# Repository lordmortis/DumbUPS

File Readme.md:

DumbUPS - A really stupid UPS daemon for really stupid UPSs
=====================

This is a go project and firmware for interfacing with UPSs that don't have modern interfaces. 
Why? they are perfectly fine and often available second hand :)

However, this is only tested against a APC BackUPS Pro 1400 via the example arduino-based interface device,
but the existing interface should work for most dumb UPS's.

Go Program
=======
The go part of this project (this directory) has two commands:
 
 * `monitor` 
   a continuously running process that reads the  
   serial port that's connected to the UPS interface microcontroller (see Protocol below). 
   It will also emit a "pong" command every 10 seconds to reset the watchdog timer
 * `shutdown`
   send the "shut" command to the micro to turn off the power.

The [config](dumbups.conf.sample) file requires the serial port. 
The monitor daemon will use the optional "shutdown" config option to specify if it will issue a shutdown upon power loss (the default) or low battery

The Protocol
====

The protocol is very simple, the UPS interface outputs lines of text representing the state:
```
STATUS-BATT:<bool>,BATTLOW:<bool>,MAINSDWN:<bool>,MAINSUP:<bool>\n
```

where <bool> is either "Yes" or "No" if that line is high.

There is a 30-second watchdog timer, where if no command is received for this period and the UPS has no power, it will turn off.

Commands:
 * `shut` - start the power off sequence if the mains power is off
 * `noshut` - cancel a power off sequence
 * `ping` - a no-op that resets the watchdog timer

UPS Interfaces
====

 * [APC - Arduino](Arduino/APC_Interface/Readme.md)
   * This implementation example uses an arduino (specifically a [LeoStick](https://www.freetronics.com.au/products/leostick)) but should be simple enough to serve as an example for other interfaces
 * [APC - attiny2312](attiny2313/Readme.md)
   * This implementation is for an [attiny2313](https://ww1.microchip.com/downloads/en/DeviceDoc/Atmel-2543-AVR-ATtiny2313_Datasheet.pdf) - which is a much simpler micro. Also includes Schematics and Gerbers for a PCB!

Linux Service
====
There is an example systemd file for running this as a linux service [here](systemd/dumbups.service)

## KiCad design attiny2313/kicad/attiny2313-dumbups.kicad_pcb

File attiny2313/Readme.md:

DumbUPS - Firmware for APC Dumb ups interface (attiny version)
=====================

This repo contains a platformio project to provide a DumbUPS serial interface for a APC UPS that uses the dumb interface.

This uses [Attiny2313V-10PU](https://ww1.microchip.com/downloads/en/DeviceDoc/Atmel-2543-AVR-ATtiny2313_Datasheet.pdf) and a [FTDI MM232R USB dev board](https://ftdichip.com/products/mm232r/) instead of a Leostick. 
I think this is a much smaller physical layout, with cheaper components and no surface mount, so this is easy to make.

Included is the [Kicad Project](kicad)

 * [Schematic](Schematic.pdf)
 * [PCB Layout](PCB.pdf)
 
Pinouts
=

| Signal        | AVR Pin       | Direction  | APC DB-9 Pin       | 
|---------------|---------------|------------|--------------------|
| Battery Power | 12 (Port B 0) | To AVR     | 2                  |
| Mains Down    | 13 (Port B 1) | To Arduino | 3 (Open Collector) |
| Ground        | 10 (Gnd)      | n/a        | 4                  |
| Low Battery   | 14 (Port B 2) | To Arduino | 5 (Open Collector) |
| Mains Up      | 15 (Port B 3) | To Arduino | 6 (Open Collector) |
| Power State   | 5 (Port A 0)  | To APC     | 7                  |

(thanks to [APCUPSD](http://apcupsd.org/manual/manual.html#voltage-signalling) for this info, made life a lot easier!)

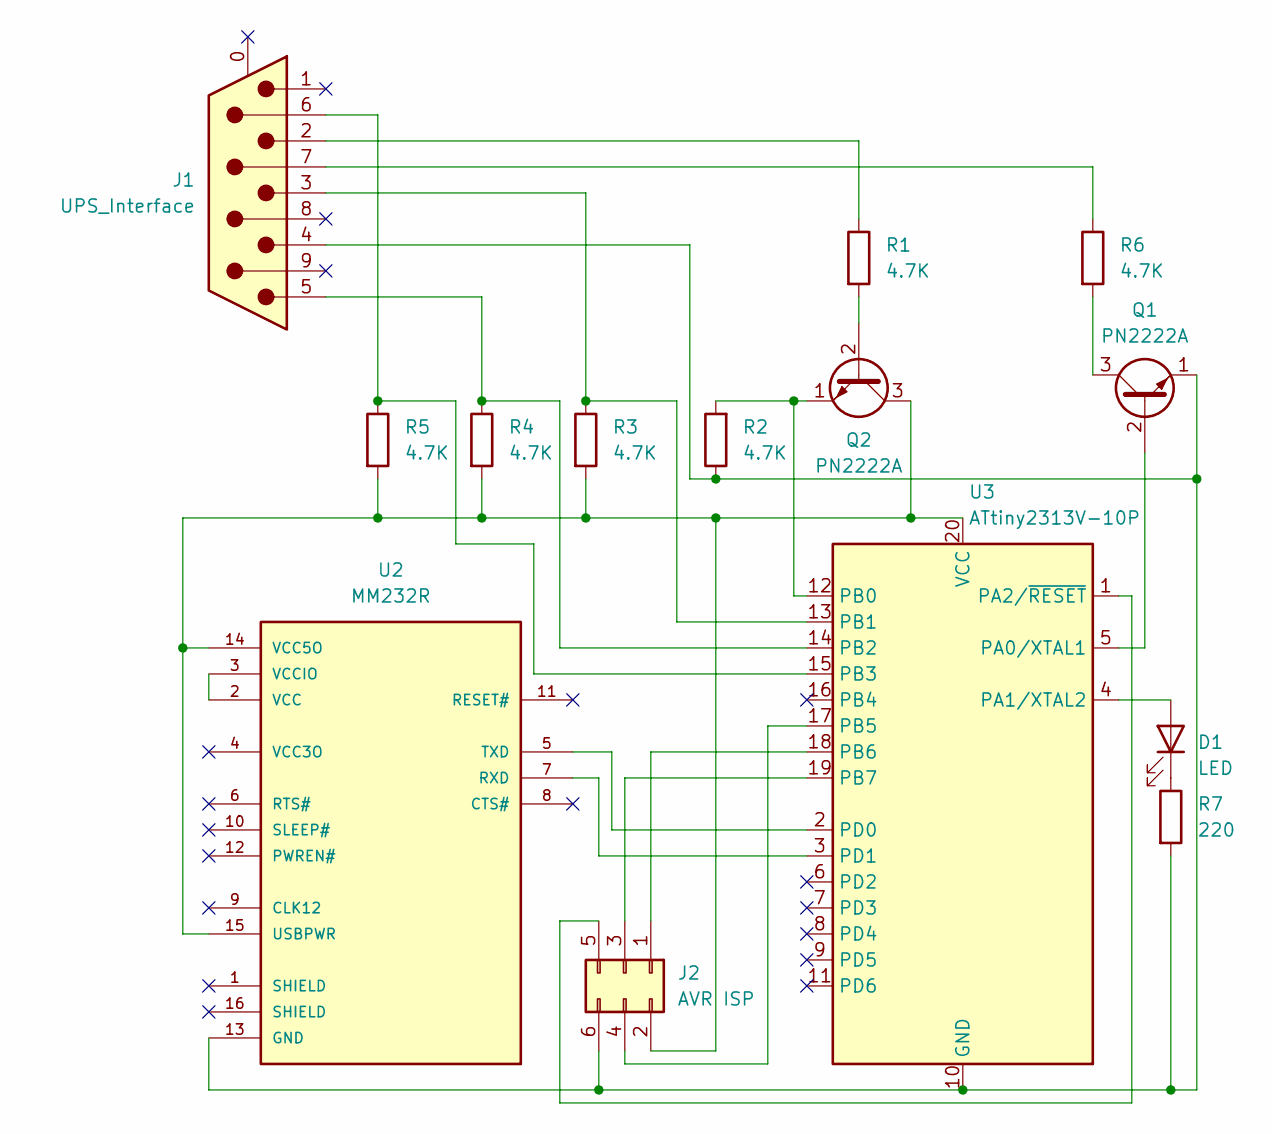
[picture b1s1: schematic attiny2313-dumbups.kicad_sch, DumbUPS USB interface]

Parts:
D1: LED; PinHeader_1x02_P2.54mm_Vertical
J1: UPS_Interface; DSUB-9_Male_Horizontal_P2.77x2.84mm_EdgePinOffset7.70mm_Hou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
J2: AVR ISP; IDC-Header_2x03_P2.54mm_Vertical
Q1: PN2222A; TO-92L_Inline
Q2: PN2222A; TO-92_Inline
R1, R2, R3, R4, R5, R6: 4.7K; R_Axial_DIN0207_L6.3mm_D2.5mm_P10.16mm_Horizontal
R7: 220; R_Axial_DIN0207_L6.3mm_D2.5mm_P10.16mm_Horizontal
U2: MM232R; FTDI_MM232R; PARTREV 1.2
U3: ATtiny2313V-10P; DIP-20_W7.62mm

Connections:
unnamed: D1.1 (K), R7.1
unnamed: D1.2 (A), U3.4 (PA1/XTAL2)
unnamed: J1.2, R1.1
unnamed: J1.3, R3.1, U3.13 (PB1)
unnamed: J1.4, J2.6, Q1.1 (E), R2.1, R7.2, U2.13 (GND), U3.10 (GND)
unnamed: J1.5, R4.1, U3.14 (PB2)
unnamed: J1.6, R5.1, U3.15 (PB3)
unnamed: J1.7, R6.1
unnamed: J2.1, U3.18 (PB6)
unnamed: J2.2, Q2.3 (C), R3.2, R4.2, R5.2, U2.14 (VCC5O), U2.15 (USBPWR), U3.20 (VCC)
unnamed: J2.3, U3.19 (PB7)
unnamed: J2.4, U3.17 (PB5)
unnamed: J2.5, U3.1 (PA2/~RESET)
unnamed: Q1.2 (B), U3.5 (PA0/XTAL1)
unnamed: Q1.3 (C), R6.2
unnamed: Q2.1 (E), R2.2, U3.12 (PB0)
unnamed: Q2.2 (B), R1.2
unnamed: U2.2 (VCC), U2.3 (VCCIO)
unnamed: U2.5 (TXD), U3.2 (PD0)
unnamed: U2.7 (RXD), U3.3 (PD1)

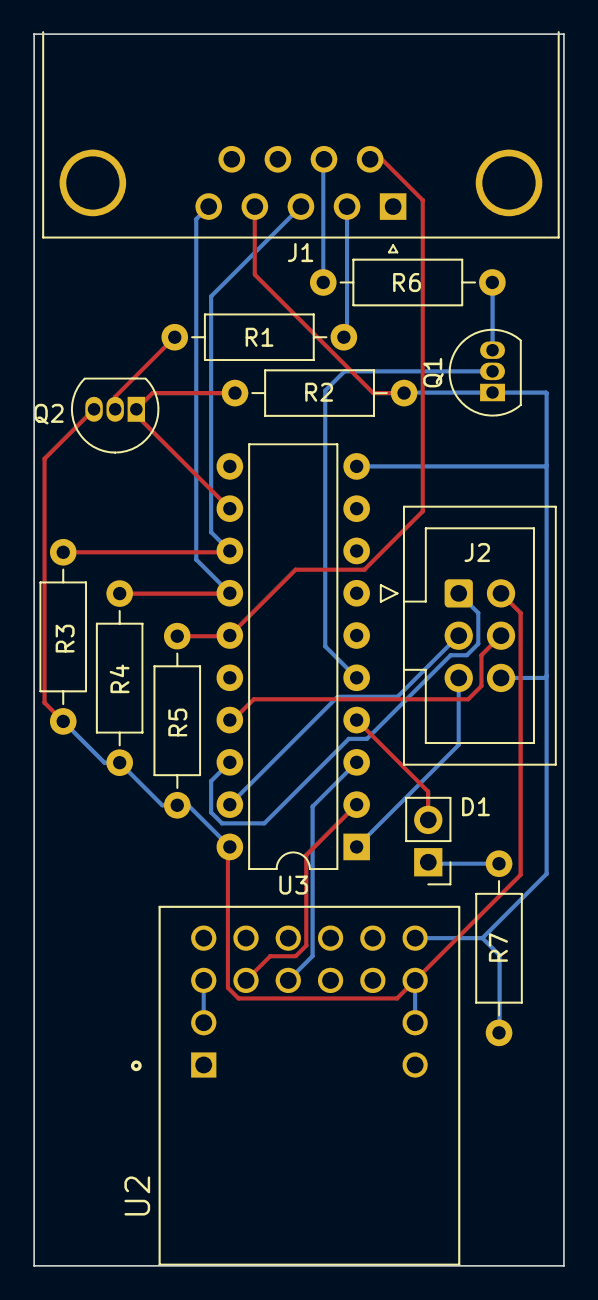
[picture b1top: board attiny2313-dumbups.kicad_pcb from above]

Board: 2 copper layers, 31.8 x 74.0 mm, 14 parts (0 on the bottom side), 20 nets.

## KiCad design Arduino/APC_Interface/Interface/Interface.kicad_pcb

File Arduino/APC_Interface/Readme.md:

DumbUPS - Firmware for APC Dumb ups interface
=====================

This repo contains a platformio project to provide a DumbUPS serial interface for a APC UPS that uses the dumb interfaces

The circuit for this is [here](Schematic.pdf)

Pinouts
=

| Signal        | Arduino Pin | Direction  | APC DB-9 Pin        |
|---------------|-------------|------------|---------------------|
| Battery Power | 8           | To Arduino | 2                   |
| Mains Down    | 10          | To Arduino | 3 (Open Collector)  |
| Ground        | Gnd         | n/a        | 4                   |
| Low Battery   | 9           | To Arduino | 5 (Open Collector)  |
| Mains Up      | 11          | To Arduino | 6  (Open Collector) |
| Power State   | 12          | To APC     | 7                   |

(thanks to [APCUPSD](http://apcupsd.org/manual/manual.html#voltage-signalling) for this info, made life a lot easier!)

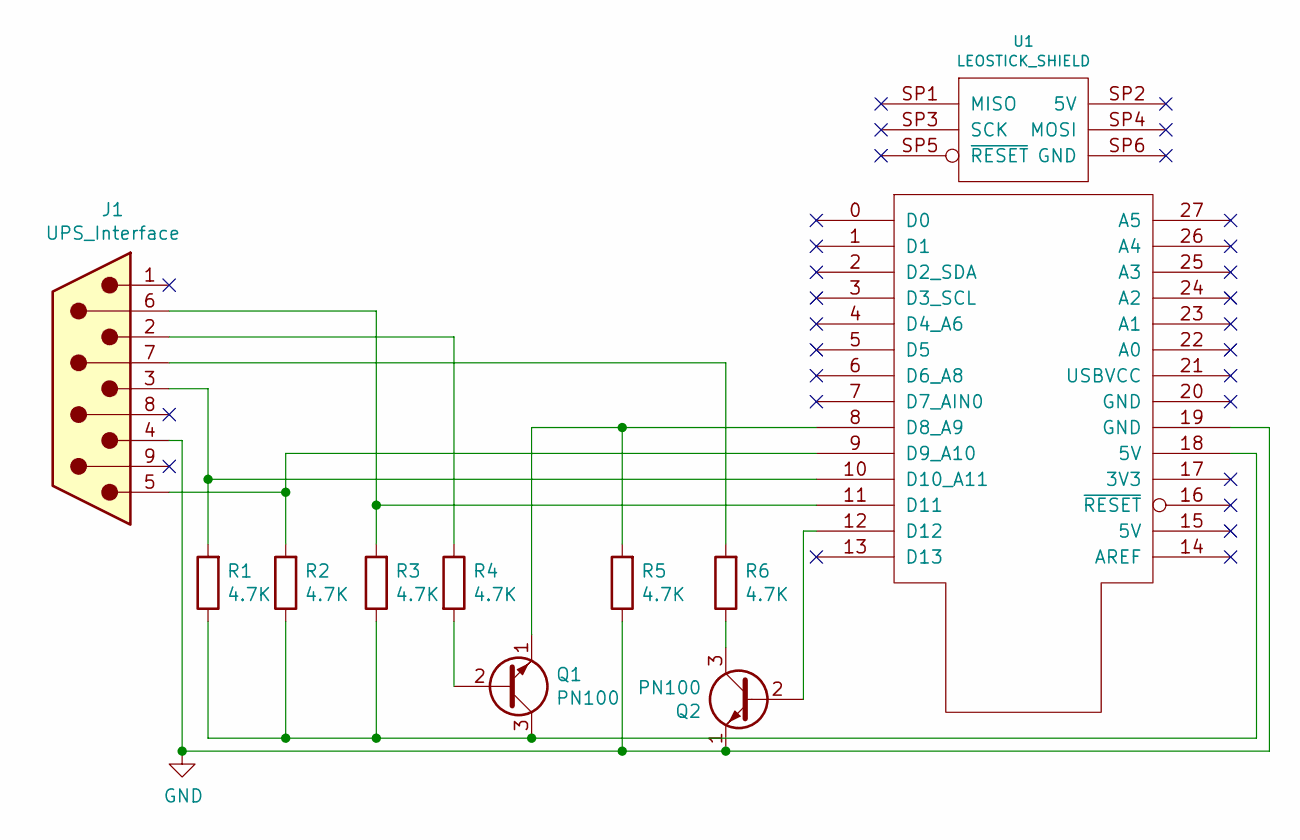
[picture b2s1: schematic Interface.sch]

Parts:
J1: UPS_Interface; DSUB-9_Male_Horizontal_P2.77x2.84mm_EdgePinOffset7.70mm_Hou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
Q1, Q2: PN100; TO-92Flat
R1, R2, R3, R4, R5, R6: 4.7K; R_Axial_DIN0207_L6.3mm_D2.5mm_P10.16mm_Horizontal
U1: LEOSTICK_SHIELD

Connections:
GND: J1.4, Q2.1 (E), R5.1, U1.19 (GND)
unnamed: J1.2, R4.1
unnamed: J1.3, R1.2, U1.10 (D10_A11)
unnamed: J1.5, R2.2, U1.9 (D9_A10)
unnamed: J1.6, R3.2, U1.11 (D11)
unnamed: J1.7, R6.2
unnamed: Q1.1 (E), R5.2, U1.8 (D8_A9)
unnamed: Q1.2 (B), R4.2
unnamed: Q1.3 (C), R1.1, R2.1, R3.1, U1.18 (5V)
unnamed: Q2.2 (B), U1.12 (D12)
unnamed: Q2.3 (C), R6.1

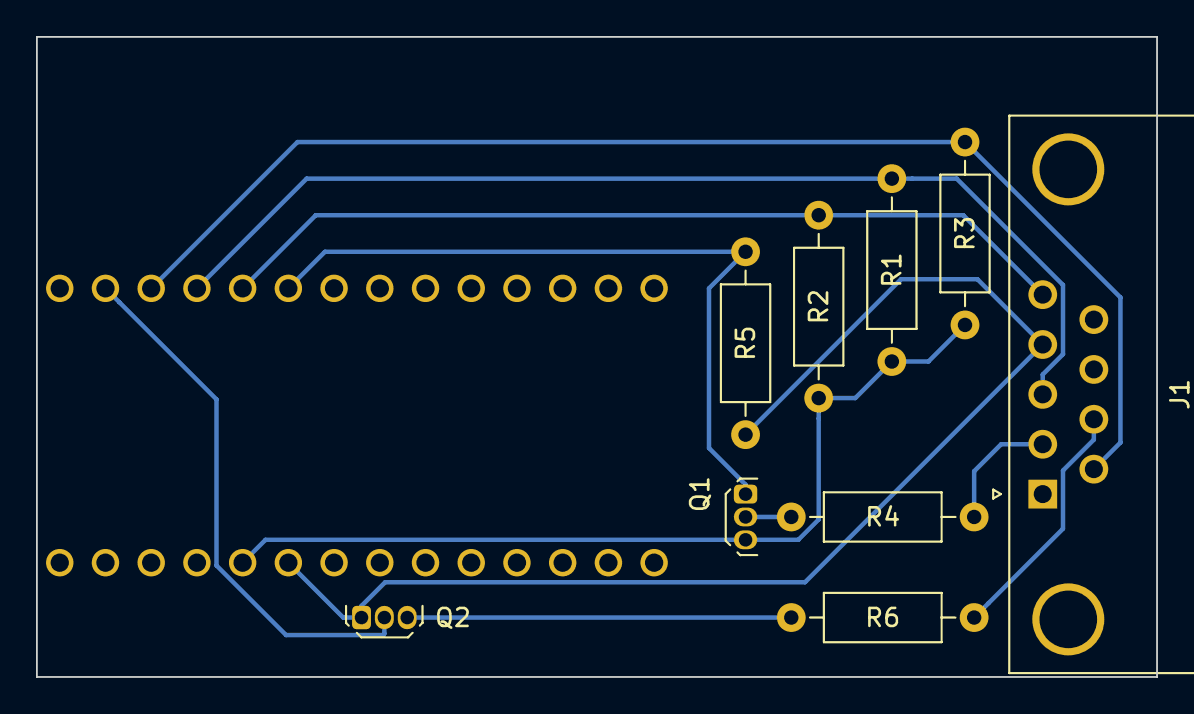
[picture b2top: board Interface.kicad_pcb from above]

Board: 2 copper layers, 62.2 x 35.6 mm, 10 parts (0 on the bottom side), 11 nets.

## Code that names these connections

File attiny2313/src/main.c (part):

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#define POWER_DOWN_FLASH_DELAY_MS 125
#define MAINS_DOWN_FLASH_DELAY_MS 50

#define POWER_STATE_BIT PA0 // Power state is Port A 0 (Output)
#define STATUS_LED_BIT PA1 // Status LED is Port A 1 (Output)

#define BATTERY_POWER_BIT PB0 // Battery Power is Port B 0 (Input)
#define MAINS_DOWN_BIT PB1 // Mains Down is Port B 1 (Input)
#define LOW_BATTERY_BIT PB2 // Low Battery is Port B 2 (Input)
#define MAINS_UP_BIT PB3 // Mains up is Port B 3 (input)

const char status_text[] PROGMEM = "STATUS-";
char const battery_text[] PROGMEM = "BATT:";
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
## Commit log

2020-02-16 Initial arduino code
2020-02-16 Go project skeleton
2020-02-16 Add command for resuming UPS power.
2020-02-16 parsing and shutdown issuance
2020-02-16 debounce and ac power resume attempt
2020-02-16 add proper shutdown commands for each OS
2020-02-20 Change to Platform IO toolchain
2020-02-22 add freetronics kicad library
2020-02-22 Add kicad files and schematic. update readme
2020-02-22 fix pinouts and resume power code
2020-02-22 add shutdown command
2020-02-22 increase power off delay, fix linux commands for shutdown
2020-02-22 Update schematic and create PCB layout
2020-02-22 remote extraneous backup file
2020-02-22 link schematic to readme
2020-02-22 Add main readme
2020-02-22 credit to APCUPSd
2020-02-23 Updated schematic and readme
2020-02-23 update with watchdog timer
2020-02-23 add systemd unit file
2020-03-02 Updated schematic & layout, floating ground
2021-12-31 add blinkenlights attiny
2022-01-01 set fuses properly for 8Mhz operation
2022-01-01 basic Serial IO
2022-01-01 blinkenlights plus more reasonable serialIO
2022-01-01 handle serial IO and command parsing.
2022-01-02 add kicad project
2022-01-02 add notes and updated docs from PCB creation
2022-01-02 cleanup readme in old APC interface thing
2022-01-02 update main readme
2022-01-02 Add status LED to board layout
2022-01-02 better string handling. start defining inputs and handling commands
2022-01-02 fix inut updates
2022-01-03 LED correct way around on schematic etc
2022-01-03 finalized firmware
2022-01-03 fixed gitignore for backups
2022-01-08 Move more functions out of timer ISR, fix serial read issues
2022-01-08 Status LED fixes
